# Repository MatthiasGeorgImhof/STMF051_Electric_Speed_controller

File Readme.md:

An ESC (electronic speed controller) and serveo breakout board using 8 PWM inputs lines (1&2 ESC, 3-8 servos 1-6)

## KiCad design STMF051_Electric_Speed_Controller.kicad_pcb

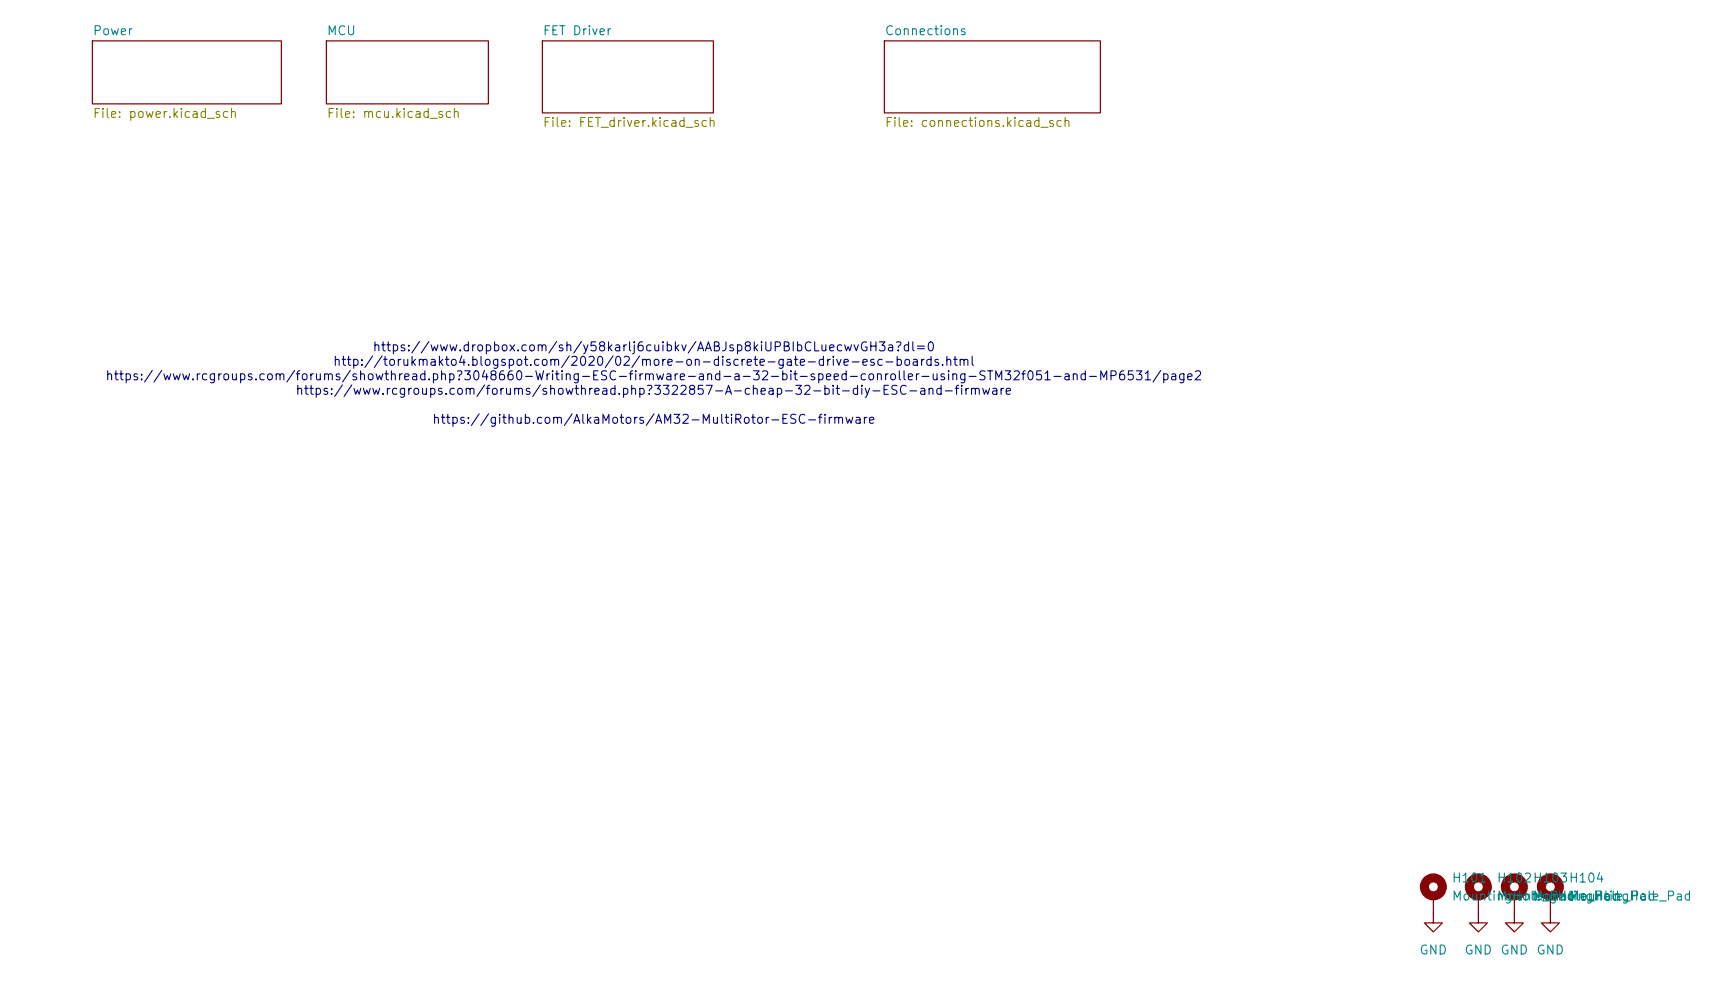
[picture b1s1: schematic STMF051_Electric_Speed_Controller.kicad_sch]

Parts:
H101, H102, H103, H104: MountingHole_Pad; MountingHole_4.3mm_M4_Pad_Via_Custom

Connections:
GND: H101.1, H102.1, H103.1, H104.1; also elsewhere on the board

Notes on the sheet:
https://www.dropbox.com/sh/y58karlj6cuibkv/AABJsp8kiUPBIbCLuecwvGH3a?dl=0 http://torukmakto4.blogspot.com/2020/02/more-on-discrete-gate-drive-esc-boards.html https://www.rcgroups.com/forums/showthread.php?3048660-Writing-ESC-firmware-and-a-32-bit-speed-conroller-using-STM32f051-and-MP6531/page2 htt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

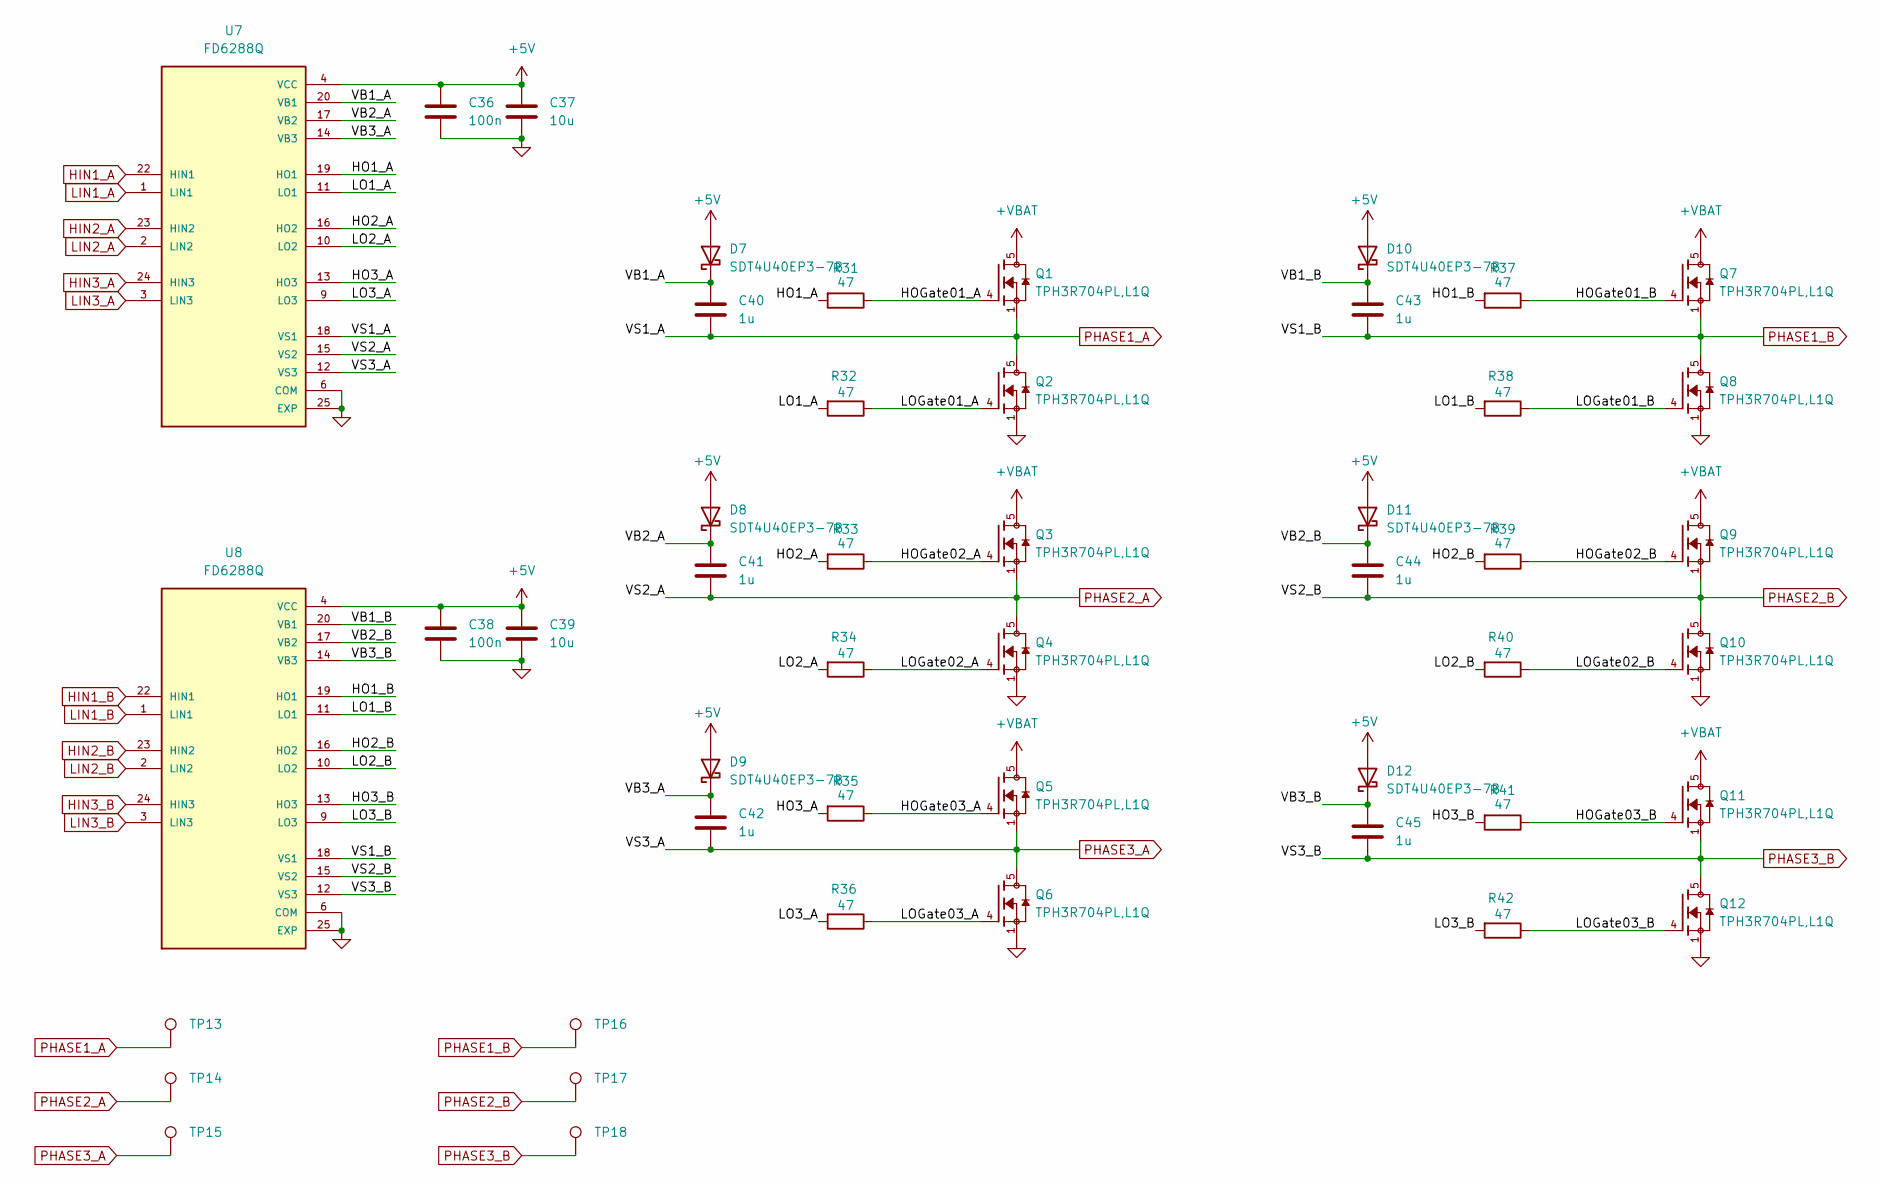
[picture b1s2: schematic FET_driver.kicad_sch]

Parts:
C36, C38: 100n; C_0402_1005Metric; Voltage 50; Tolerance 10%; Part Number GRM155R61H104KE14D
C37, C39: 10u; C_0805_2012Metric; Voltage 50; Tolerance 10%; Part Number GRM21BR61H106KE43L
C40, C41, C42, C43, C44, C45: 1u; C_0402_1005Metric; Voltage 50; Tolerance 10%; Part Number GRM155R61H105KE05D
D7, D8, D9, D10, D11, D12: SDT4U40EP3-7B; X3-TSN1608-2; Voltage 40; Part Number SDT4U40EP3-7B
Q1, Q2, Q3, Q4, Q5, Q6, Q7, Q8, Q9, Q10, Q11, Q12: TPH3R704PL,L1Q; TRANS_TPHR8504PL_L1Q; PARTREV 3
R31, R32, R33, R34, R35, R36, R37, R38, R39, R40, R41, R42: 47; R_0603_1608Metric; Tolerance 1%; Part Number RC0603FR-0747RL
TP13, TP14, TP15, TP16, TP17, TP18: TestPoint; TestPoint_THTPad_4.0x4.0mm
U7, U8: FD6288Q; QFN50P400X400X90-25N; Part Number FD6288Q

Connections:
+5V: C36.1, C37.1, C38.1, C39.1, D7.2 (A), D8.2 (A), D9.2 (A), D10.2 (A), D11.2 (A), D12.2 (A), U7.4 (VCC), U8.4 (VCC); also elsewhere on the board
+VBAT: Q1.5, Q3.5, Q5.5, Q7.5, Q9.5, Q11.5; also elsewhere on the board
/FET Driver/HO1_A: R31.2, U7.19 (HO1)
/FET Driver/HO1_B: R37.2, U8.19 (HO1)
/FET Driver/HO2_A: R33.2, U7.16 (HO2)
/FET Driver/HO2_B: R39.2, U8.16 (HO2)
/FET Driver/HO3_A: R35.2, U7.13 (HO3)
/FET Driver/HO3_B: R41.2, U8.13 (HO3)
/FET Driver/HOGate01_A: Q1.4, R31.1
/FET Driver/HOGate01_B: Q7.4, R37.1
/FET Driver/HOGate02_A: Q3.4, R33.1
/FET Driver/HOGate02_B: Q9.4, R39.1
/FET Driver/HOGate03_A: Q5.4, R35.1
/FET Driver/HOGate03_B: Q11.4, R41.1
/FET Driver/LO1_A: R32.2, U7.11 (LO1)
/FET Driver/LO1_B: R38.2, U8.11 (LO1)
/FET Driver/LO2_A: R34.2, U7.10 (LO2)
/FET Driver/LO2_B: R40.2, U8.10 (LO2)
/FET Driver/LO3_A: R36.2, U7.9 (LO3)
/FET Driver/LO3_B: R42.2, U8.9 (LO3)
/FET Driver/LOGate01_A: Q2.4, R32.1
/FET Driver/LOGate01_B: Q8.4, R38.1
/FET Driver/LOGate02_A: Q4.4, R34.1
/FET Driver/LOGate02_B: Q10.4, R40.1
/FET Driver/LOGate03_A: Q6.4, R36.1
/FET Driver/LOGate03_B: Q12.4, R42.1
/FET Driver/VB1_A: C40.1, D7.1 (K), U7.20 (VB1)
/FET Driver/VB1_B: C43.1, D10.1 (K), U8.20 (VB1)
/FET Driver/VB2_A: C41.1, D8.1 (K), U7.17 (VB2)
/FET Driver/VB2_B: C44.1, D11.1 (K), U8.17 (VB2)
/FET Driver/VB3_A: C42.1, D9.1 (K), U7.14 (VB3)
/FET Driver/VB3_B: C45.1, D12.1 (K), U8.14 (VB3)
GND: C36.2, C37.2, C38.2, C39.2, Q2.1, Q4.1, Q6.1, Q8.1, Q10.1, Q12.1, U7.6 (COM), U7.25 (EXP), U8.6 (COM), U8.25 (EXP); also elsewhere on the board
HIN1_A: U7.22 (HIN1); also elsewhere on the board
HIN1_B: U8.22 (HIN1); also elsewhere on the board
HIN2_A: U7.23 (HIN2); also elsewhere on the board
HIN2_B: U8.23 (HIN2); also elsewhere on the board
HIN3_A: U7.24 (HIN3); also elsewhere on the board
HIN3_B: U8.24 (HIN3); also elsewhere on the board
LIN1_A: U7.1 (LIN1); also elsewhere on the board
LIN1_B: U8.1 (LIN1); also elsewhere on the board
LIN2_A: U7.2 (LIN2); also elsewhere on the board
LIN2_B: U8.2 (LIN2); also elsewhere on the board
LIN3_A: U7.3 (LIN3); also elsewhere on the board
LIN3_B: U8.3 (LIN3); also elsewhere on the board
PHASE1_A: C40.2, Q1.1, Q2.5, TP13.1, U7.18 (VS1); also elsewhere on the board
PHASE1_B: C43.2, Q7.1, Q8.5, TP16.1, U8.18 (VS1); also elsewhere on the board
PHASE2_A: C41.2, Q3.1, Q4.5, TP14.1, U7.15 (VS2); also elsewhere on the board
PHASE2_B: C44.2, Q9.1, Q10.5, TP17.1, U8.15 (VS2); also elsewhere on the board
PHASE3_A: C42.2, Q5.1, Q6.5, TP15.1, U7.12 (VS3); also elsewhere on the board
PHASE3_B: C45.2, Q11.1, Q12.5, TP18.1, U8.12 (VS3); also elsewhere on the board

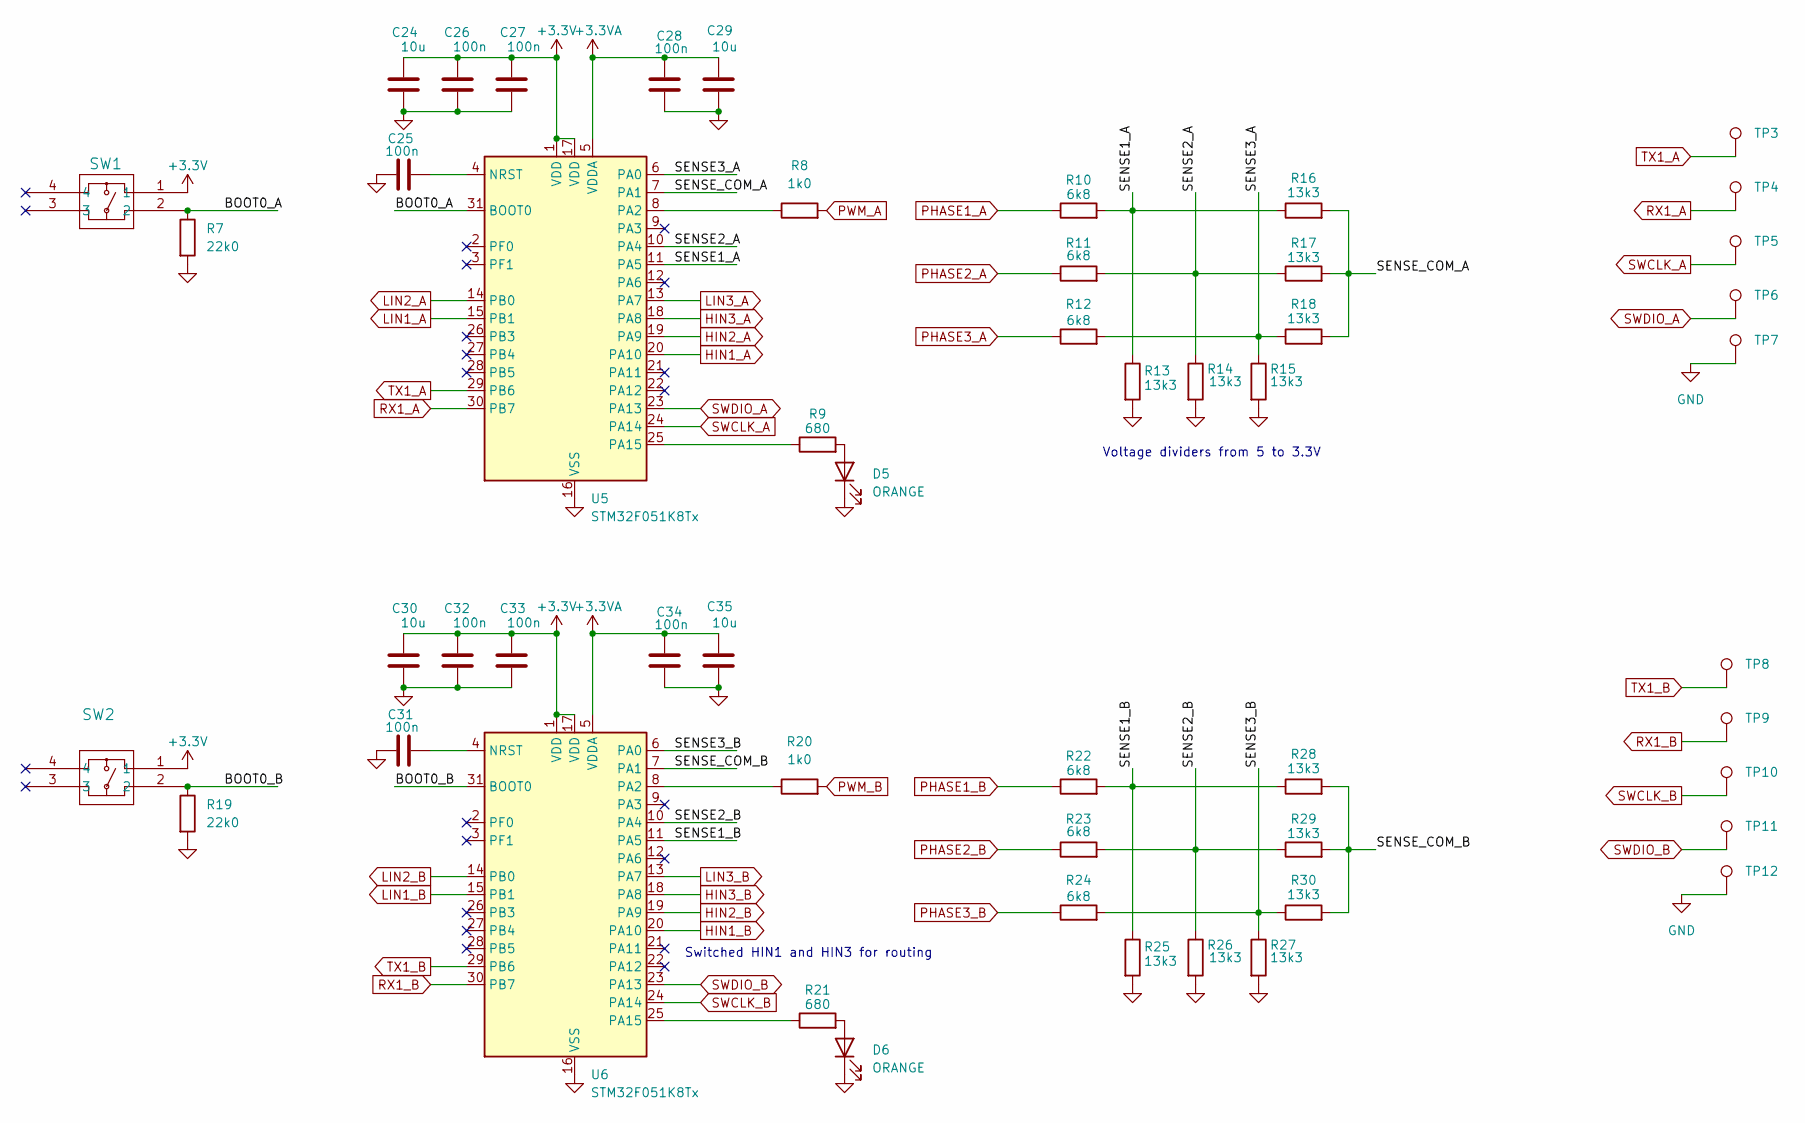
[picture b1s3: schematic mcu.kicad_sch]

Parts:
C24, C29, C30, C35: 10u; C_0603_1608Metric; Voltage 25; Tolerance 10%; Part Number GRM188R61E106KA73D
C25, C26, C27, C28, C31, C32, C33, C34: 100n; C_0402_1005Metric; Voltage 50; Tolerance 10%; Part Number GRM155R61H104KE14D
D5, D6: ORANGE; LED_0603_1608Metric; Voltage 2; Part Number LTST-C191KFKT
R7, R19: 22k0; R_0201_0603Metric; Tolerance 1%; Part Number RC0402FR-0722KL
R8, R20: 1k0; R_0201_0603Metric; Tolerance 1%; Part Number RC0402FR-071KL
R9, R21: 680; R_0201_0603Metric; Tolerance 1%; Part Number RC0402FR-13680RL
R10, R11, R12, R22, R23, R24: 6k8; R_0201_0603Metric; Tolerance 1%; Part Number RC0201FR-076K8L
R13, R14, R15, R16, R17, R18, R25, R26, R27, R28, R29, R30: 13k3; R_0201_0603Metric; Tolerance 1%; Part Number RC0201FR-0713K3L
SW1, SW2: EVPAA602; Part Number EVP-AA602W
TP3, TP4, TP5, TP6, TP8, TP9, TP10, TP11: TestPoint; TestPoint_Pad_1.0x1.0mm
TP7, TP12: TestPoint; TestPoint_Pad_1.0x1.5mm
U5, U6: STM32F051K8Tx; LQFP-32_7x7mm_P0.8mm; Part Number STM32F051K8T6

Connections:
+3.3V: C24.1, C26.1, C27.1, C30.1, C32.1, C33.1, SW1.1, SW2.1, U5.1 (VDD), U5.17 (VDD), U6.1 (VDD), U6.17 (VDD); also elsewhere on the board
+3.3VA: C28.1, C29.1, C34.1, C35.1, U5.5 (VDDA), U6.5 (VDDA); also elsewhere on the board
/MCU/BOOT0_A: R7.1, SW1.2, U5.31 (BOOT0)
/MCU/BOOT0_B: R19.1, SW2.2, U6.31 (BOOT0)
/MCU/SENSE1_A: R10.2, R13.1, R16.1, U5.11 (PA5)
/MCU/SENSE1_B: R22.2, R25.1, R28.1, U6.11 (PA5)
/MCU/SENSE2_A: R11.2, R14.1, R17.1, U5.10 (PA4)
/MCU/SENSE2_B: R23.2, R26.1, R29.1, U6.10 (PA4)
/MCU/SENSE3_A: R12.2, R15.1, R18.1, U5.6 (PA0)
/MCU/SENSE3_B: R24.2, R27.1, R30.1, U6.6 (PA0)
/MCU/SENSE_COM_A: R16.2, R17.2, R18.2, U5.7 (PA1)
/MCU/SENSE_COM_B: R28.2, R29.2, R30.2, U6.7 (PA1)
GND: C24.2, C25.1, C26.2, C27.2, C28.2, C29.2, C30.2, C31.1, C32.2, C33.2, C34.2, C35.2, D5.1 (K), D6.1 (K), R7.2, R13.2, R14.2, R15.2, R19.2, R25.2, R26.2, R27.2, TP7.1, TP12.1, U5.16 (VSS), U5.32 (VSS), U6.16 (VSS), U6.32 (VSS); also elsewhere on the board
HIN1_A: U5.20 (PA10); also elsewhere on the board
HIN1_B: U6.20 (PA10); also elsewhere on the board
HIN2_A: U5.19 (PA9); also elsewhere on the board
HIN2_B: U6.19 (PA9); also elsewhere on the board
HIN3_A: U5.18 (PA8); also elsewhere on the board
HIN3_B: U6.18 (PA8); also elsewhere on the board
LIN1_A: U5.15 (PB1); also elsewhere on the board
LIN1_B: U6.15 (PB1); also elsewhere on the board
LIN2_A: U5.14 (PB0); also elsewhere on the board
LIN2_B: U6.14 (PB0); also elsewhere on the board
LIN3_A: U5.13 (PA7); also elsewhere on the board
LIN3_B: U6.13 (PA7); also elsewhere on the board
unnamed: D5.2 (A), R9.2
unnamed: D6.2 (A), R21.2
unnamed: C25.2, U5.4 (NRST)
unnamed: R8.1, U5.8 (PA2)
unnamed: R9.1, U5.25 (PA15)
unnamed: C31.2, U6.4 (NRST)
unnamed: R20.1, U6.8 (PA2)
unnamed: R21.1, U6.25 (PA15)
PHASE1_A: R10.1; also elsewhere on the board
PHASE1_B: R22.1; also elsewhere on the board
PHASE2_A: R11.1; also elsewhere on the board
PHASE2_B: R23.1; also elsewhere on the board
PHASE3_A: R12.1; also elsewhere on the board
PHASE3_B: R24.1; also elsewhere on the board
PWM1: R8.2; also elsewhere on the board
PWM2: R20.2; also elsewhere on the board
RX1_A: TP4.1, U5.30 (PB7)
RX1_B: TP9.1, U6.30 (PB7)
SWCLK_A: TP5.1, U5.24 (PA14)
SWCLK_B: TP10.1, U6.24 (PA14)
SWDIO_A: TP6.1, U5.23 (PA13)
SWDIO_B: TP11.1, U6.23 (PA13)
TX1_A: TP3.1, U5.29 (PB6)
TX1_B: TP8.1, U6.29 (PB6)

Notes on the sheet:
Voltage dividers from 5 to 3.3V
Switched HIN1 and HIN3 for routing

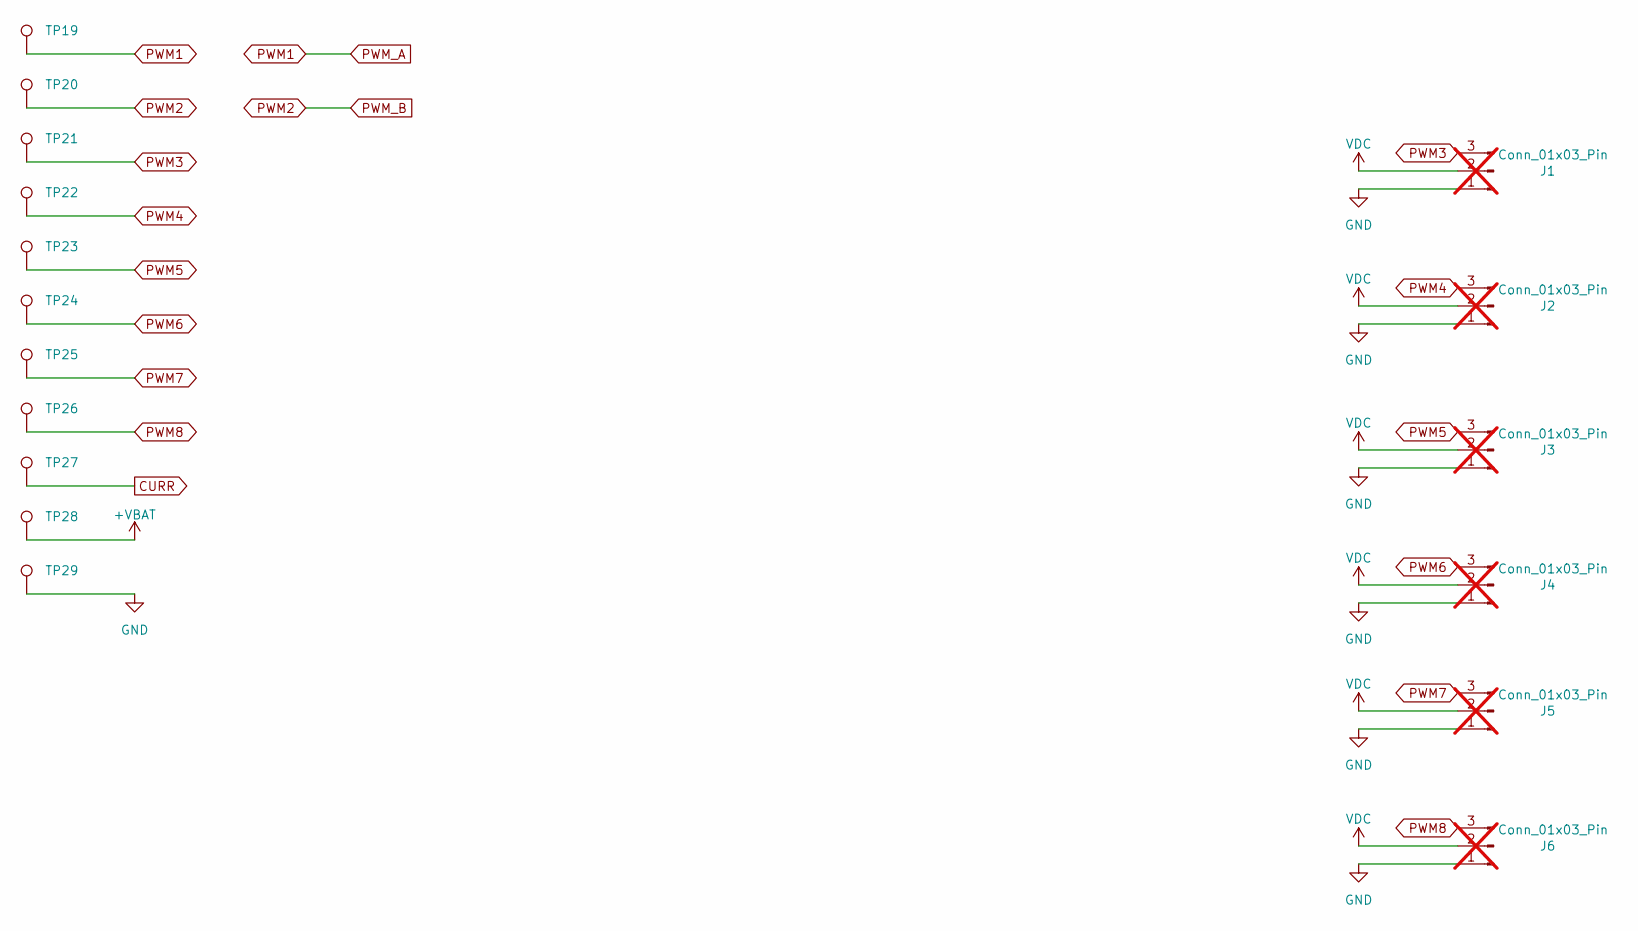
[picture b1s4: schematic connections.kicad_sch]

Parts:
J1, J2, J3, J4, J5, J6: Conn_01x03_Pin; PinHeader_1x03_P2.54mm_Vertical; not fitted
TP19, TP20, TP21, TP22, TP23, TP24, TP25, TP26, TP27: TestPoint; TestPoint_Pad_1.0x1.5mm_doublesided
TP28, TP29: TestPoint; TestPoint_Pad_1.5x1.5mm_doublesided

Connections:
+VBAT: TP28.1; also elsewhere on the board
CURR: TP27.1; also elsewhere on the board
GND: J1.1, J2.1, J3.1, J4.1, J5.1, J6.1, TP29.1; also elsewhere on the board
PWM1: TP19.1; also elsewhere on the board
PWM2: TP20.1; also elsewhere on the board
PWM3: J1.3, TP21.1
PWM4: J2.3, TP22.1
PWM5: J3.3, TP23.1
PWM6: J4.3, TP24.1
PWM7: J5.3, TP25.1
PWM8: J6.3, TP26.1
VDC: J1.2, J2.2, J3.2, J4.2, J5.2, J6.2; also elsewhere on the board

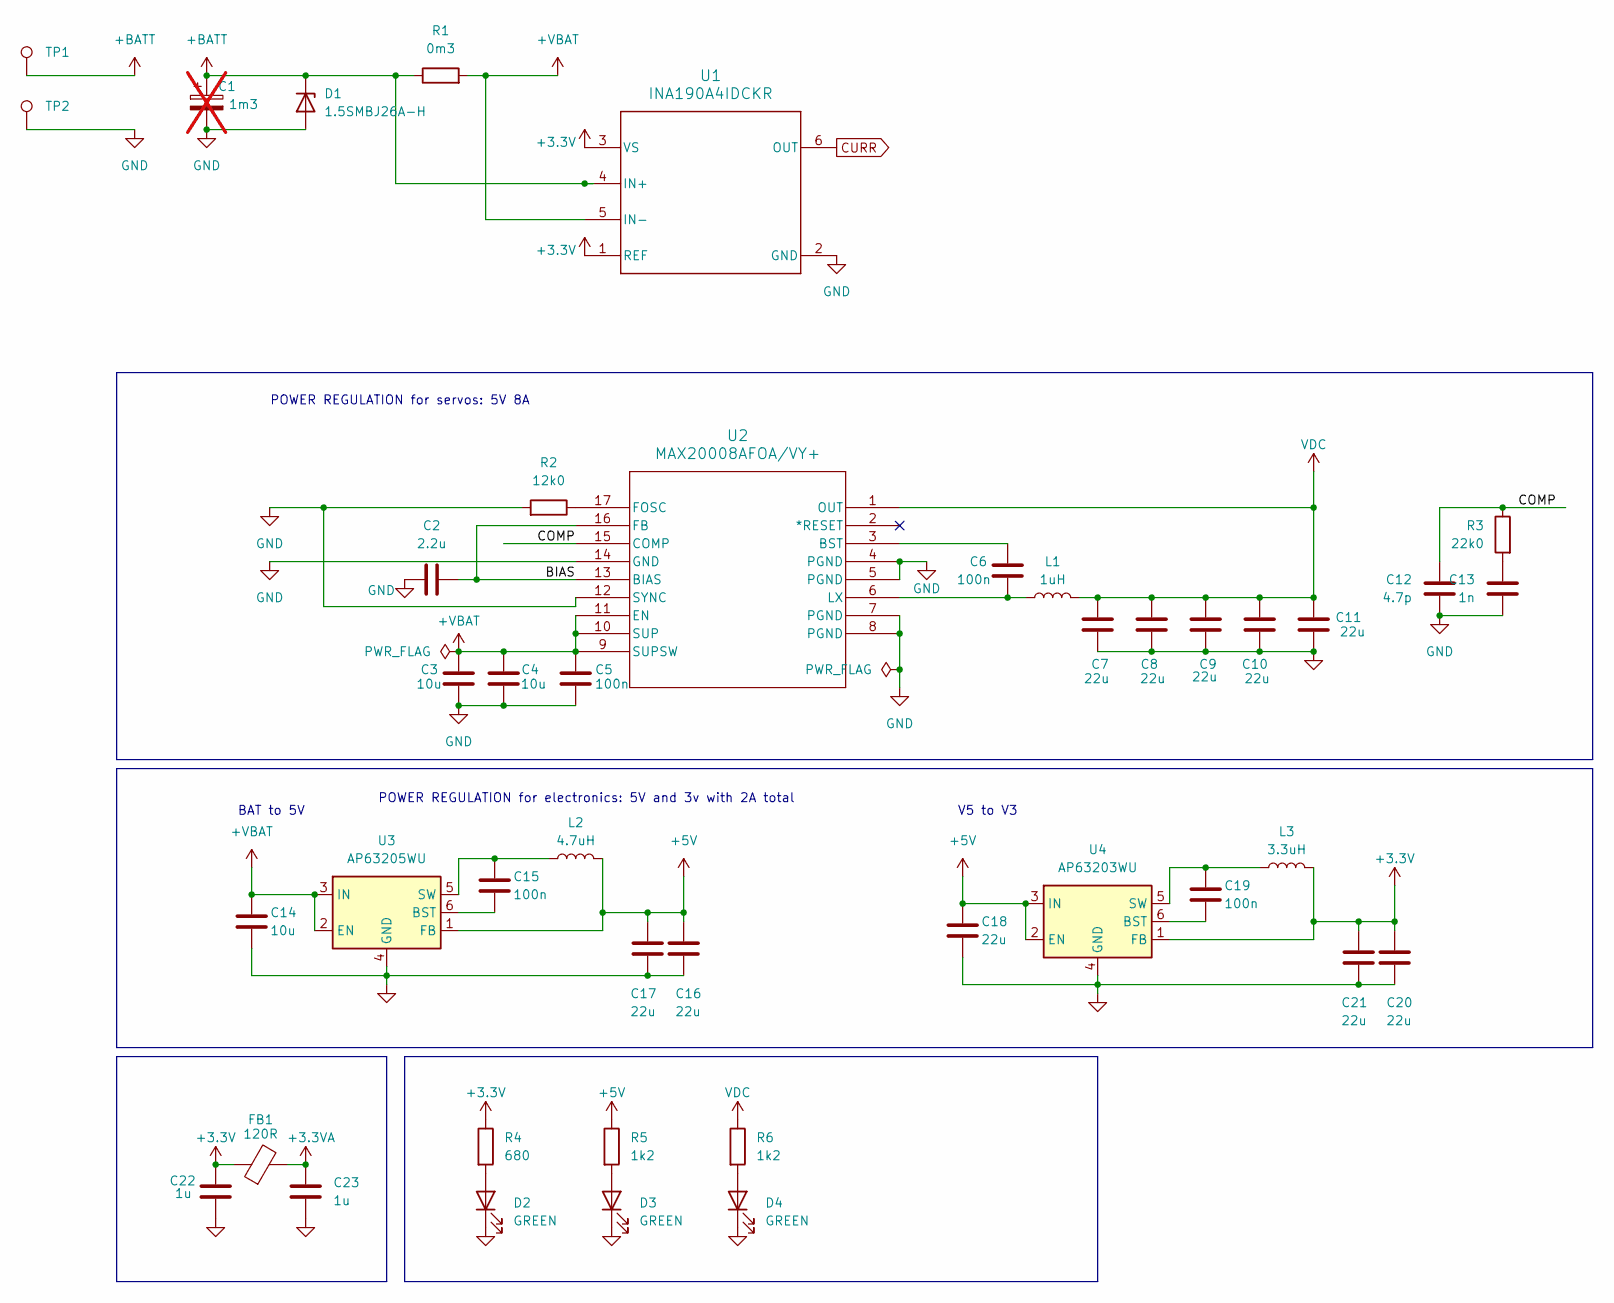
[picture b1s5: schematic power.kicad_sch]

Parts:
C1: 1m3; Tolerance 20%; Voltage 50; Part Number EGPD500ELL132MK35H; not fitted
C2: 2.2u; C_0402_1005Metric; Voltage 35; Tolerance 10%; Part Number GRM155R6YA225KE11D
C3, C4, C14: 10u; C_0805_2012Metric; Voltage 50; Tolerance 10%; Part Number GRM21BR61H106KE43L
C5, C6, C15, C19: 100n; C_0402_1005Metric; Voltage 50; Tolerance 10%; Part Number GRM155R61H104KE14D
C7, C8, C9, C10, C11, C16, C17, C18, C20, C21: 22u; C_0805_2012Metric; Voltage 25; Tolerance 20%; Part Number GRM21BR61E226ME44K
C12: 4.7p; C_0402_1005Metric; Voltage 50; Tolerance 0.25p; Part Number GRM1555C1H4R7CA01D
C13: 1n; C_0402_1005Metric; Tolerance 10%; Voltage 50; Part Number GRM155R61H102KA01D
C22, C23: 1u; C_0402_1005Metric; Voltage 50; Tolerance 10%; Part Number GRM155R61H105KE05D
D1: 1.5SMBJ26A-H; D_SMB; Voltage 42; Part Number 1.5SMBJ26A-H
D2, D3, D4: GREEN; LED_0603_1608Metric; Voltage 2; Part Number LTST-C191GKT
FB1: 120R; L_0603_1608Metric; Part Number MI0603M121R-10
L1: 1uH; SRP6540-1R0M; Part Number SRP6540-1R0M
L2: 4.7uH; L_1210_3225Metric; Part Number DFE322520FD-4R7M=P2
L3: 3.3uH; L_1210_3225Metric; Part Number DFE322512F-3R3M=P2
R1: 0m3; R_1206_3216Metric; Tolerance 1%; Part Number HCS1206FTL300
R2: 12k0; R_0201_0603Metric; Tolerance 1%; Part Number RC0402FR-0712KL
R3: 22k0; R_0201_0603Metric; Tolerance 1%; Part Number RC0402FR-0722KL
R4: 680; R_0201_0603Metric; Tolerance 1%; Part Number RC0402FR-13680RL
R5, R6: 1k2; R_0201_0603Metric; Tolerance 1%; Part Number RC0402FR-131K2L
TP1, TP2: TestPoint; TestPoint_THTPad_6.0x6.0mm_Drill1.0mm
U1: INA190A4IDCKR; DCK0006A-MFG; Part Number INA190A4IDCKR
U2: MAX20008AFOA/VY+; MAX2000x; Voltage 5; Part Number MAX20008AFOA/VY+
U3: AP63205WU; TSOT-23-6; Voltage 3; Part Number AP63205WU-7
U4: AP63203WU; TSOT-23-6; Voltage 5; Part Number AP63203WU-7

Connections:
+3.3V: C20.1, C21.1, C22.1, FB1.1, L3.2, R4.1, U1.1 (REF), U1.3 (VS), U4.1 (FB); also elsewhere on the board
+3.3VA: C23.1, FB1.2; also elsewhere on the board
+5V: C16.1, C17.1, C18.1, L2.2, R5.1, U3.1 (FB), U4.2 (EN), U4.3 (IN); also elsewhere on the board
+BATT: C1.1, D1.1 (K), R1.1, TP1.1, U1.4 (IN+)
+VBAT: C3.1, C4.1, C5.1, C14.1, R1.2, U1.5 (IN-), U2.9 (SUPSW), U2.10 (SUP), U2.11 (EN), U3.2 (EN), U3.3 (IN); also elsewhere on the board
/Power/BIAS: C2.1, U2.13 (BIAS), U2.16 (FB)
/Power/COMP: C12.1, R3.1, U2.15 (COMP)
CURR: U1.6 (OUT); also elsewhere on the board
GND: C1.2, C2.2, C3.2, C4.2, C5.2, C7.2, C8.2, C9.2, C10.2, C11.2, C12.2, C13.2, C14.2, C16.2, C17.2, C18.2, C20.2, C21.2, C22.2, C23.2, D1.2 (A), D2.1 (K), D3.1 (K), D4.1 (K), R2.2, TP2.1, U1.2 (GND), U2.4 (PGND), U2.5 (PGND), U2.7 (PGND), U2.8 (PGND), U2.12 (SYNC), U2.14 (GND), U3.4 (GND), U4.4 (GND); also elsewhere on the board
unnamed: C13.1, R3.2
unnamed: D2.2 (A), R4.2
unnamed: D3.2 (A), R5.2
unnamed: D4.2 (A), R6.2
unnamed: C6.1, U2.3 (BST)
unnamed: R2.1, U2.17 (FOSC)
unnamed: C6.2, L1.2, U2.6 (LX)
unnamed: C15.2, U3.6 (BST)
unnamed: C15.1, L2.1, U3.5 (SW)
unnamed: C19.2, U4.6 (BST)
unnamed: C19.1, L3.1, U4.5 (SW)
VDC: C7.1, C8.1, C9.1, C10.1, C11.1, L1.1, R6.1, U2.1 (OUT); also elsewhere on the board

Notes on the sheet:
POWER REGULATION for electronics: 5V and 3v with 2A total
V5 to V3
POWER REGULATION for servos: 5V 8A
BAT to 5V

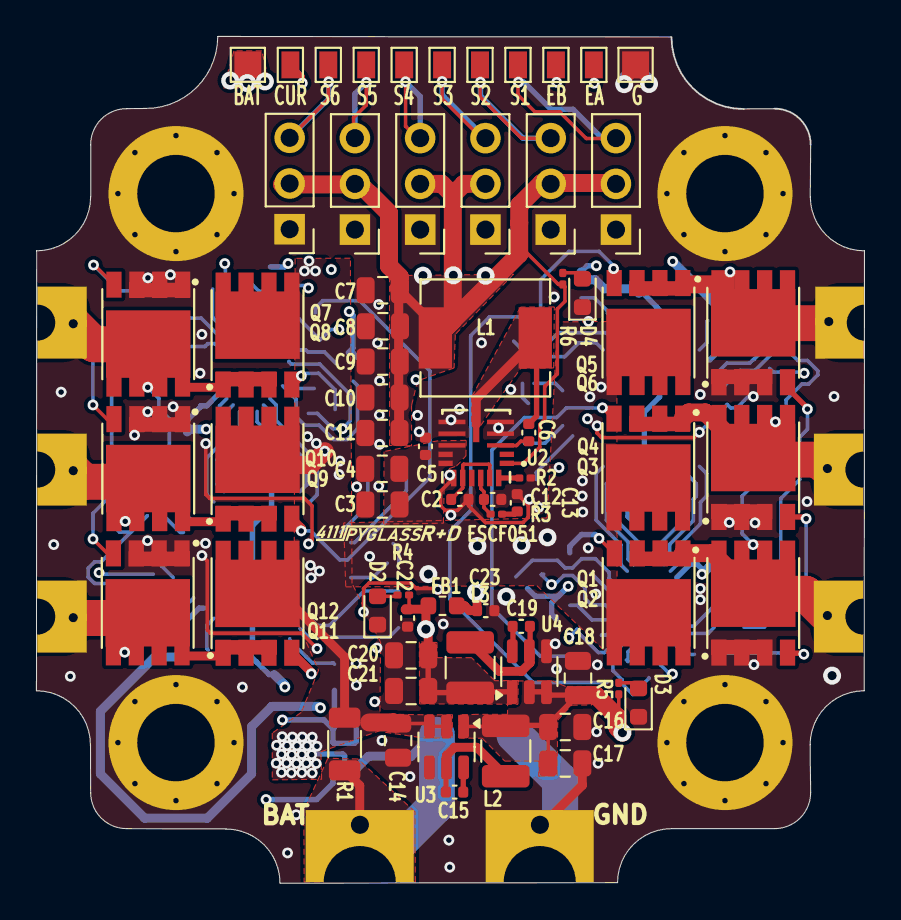
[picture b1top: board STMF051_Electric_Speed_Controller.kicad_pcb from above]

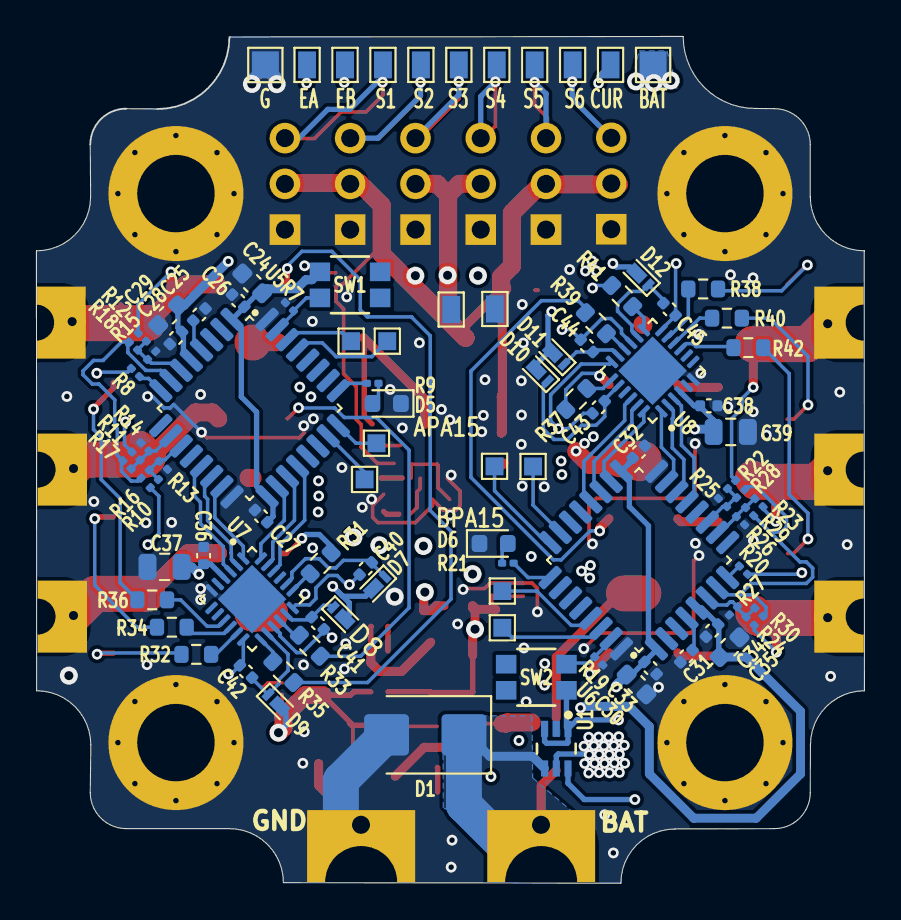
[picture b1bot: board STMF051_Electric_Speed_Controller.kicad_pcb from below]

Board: 4 copper layers, 46.0 x 47.0 mm, 163 parts (84 on the bottom side), 103 nets.

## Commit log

2024-07-21 first cleaned-up version of the ESC and servo controller project
2024-07-21 exclude lock files and add table file
2024-07-26 add logo and use 0603 LEDs
2024-07-26 change LED footprint to 0603 and change D1 to more powerful diode with same footprint
2024-07-29 edit layout A to work without blind vias by turing MC and ESC 45 to take advantage of pin layouts
2024-07-31 removed all microvias, use 0603 for driver resistors
2024-07-31 remove blind vias
2024-07-31 add gnd vias
2024-07-31 tweaks
2024-08-04 cleanup layout, silkmasks, and add connections between planes for power and gnd
2024-08-04 cleanup BOM and bump up voltage rating/footprint for capacitors to max possible
2024-08-04 change charge diodes footprint from plain 0603 to X3-TSN1608-2 which has asymetric pads
